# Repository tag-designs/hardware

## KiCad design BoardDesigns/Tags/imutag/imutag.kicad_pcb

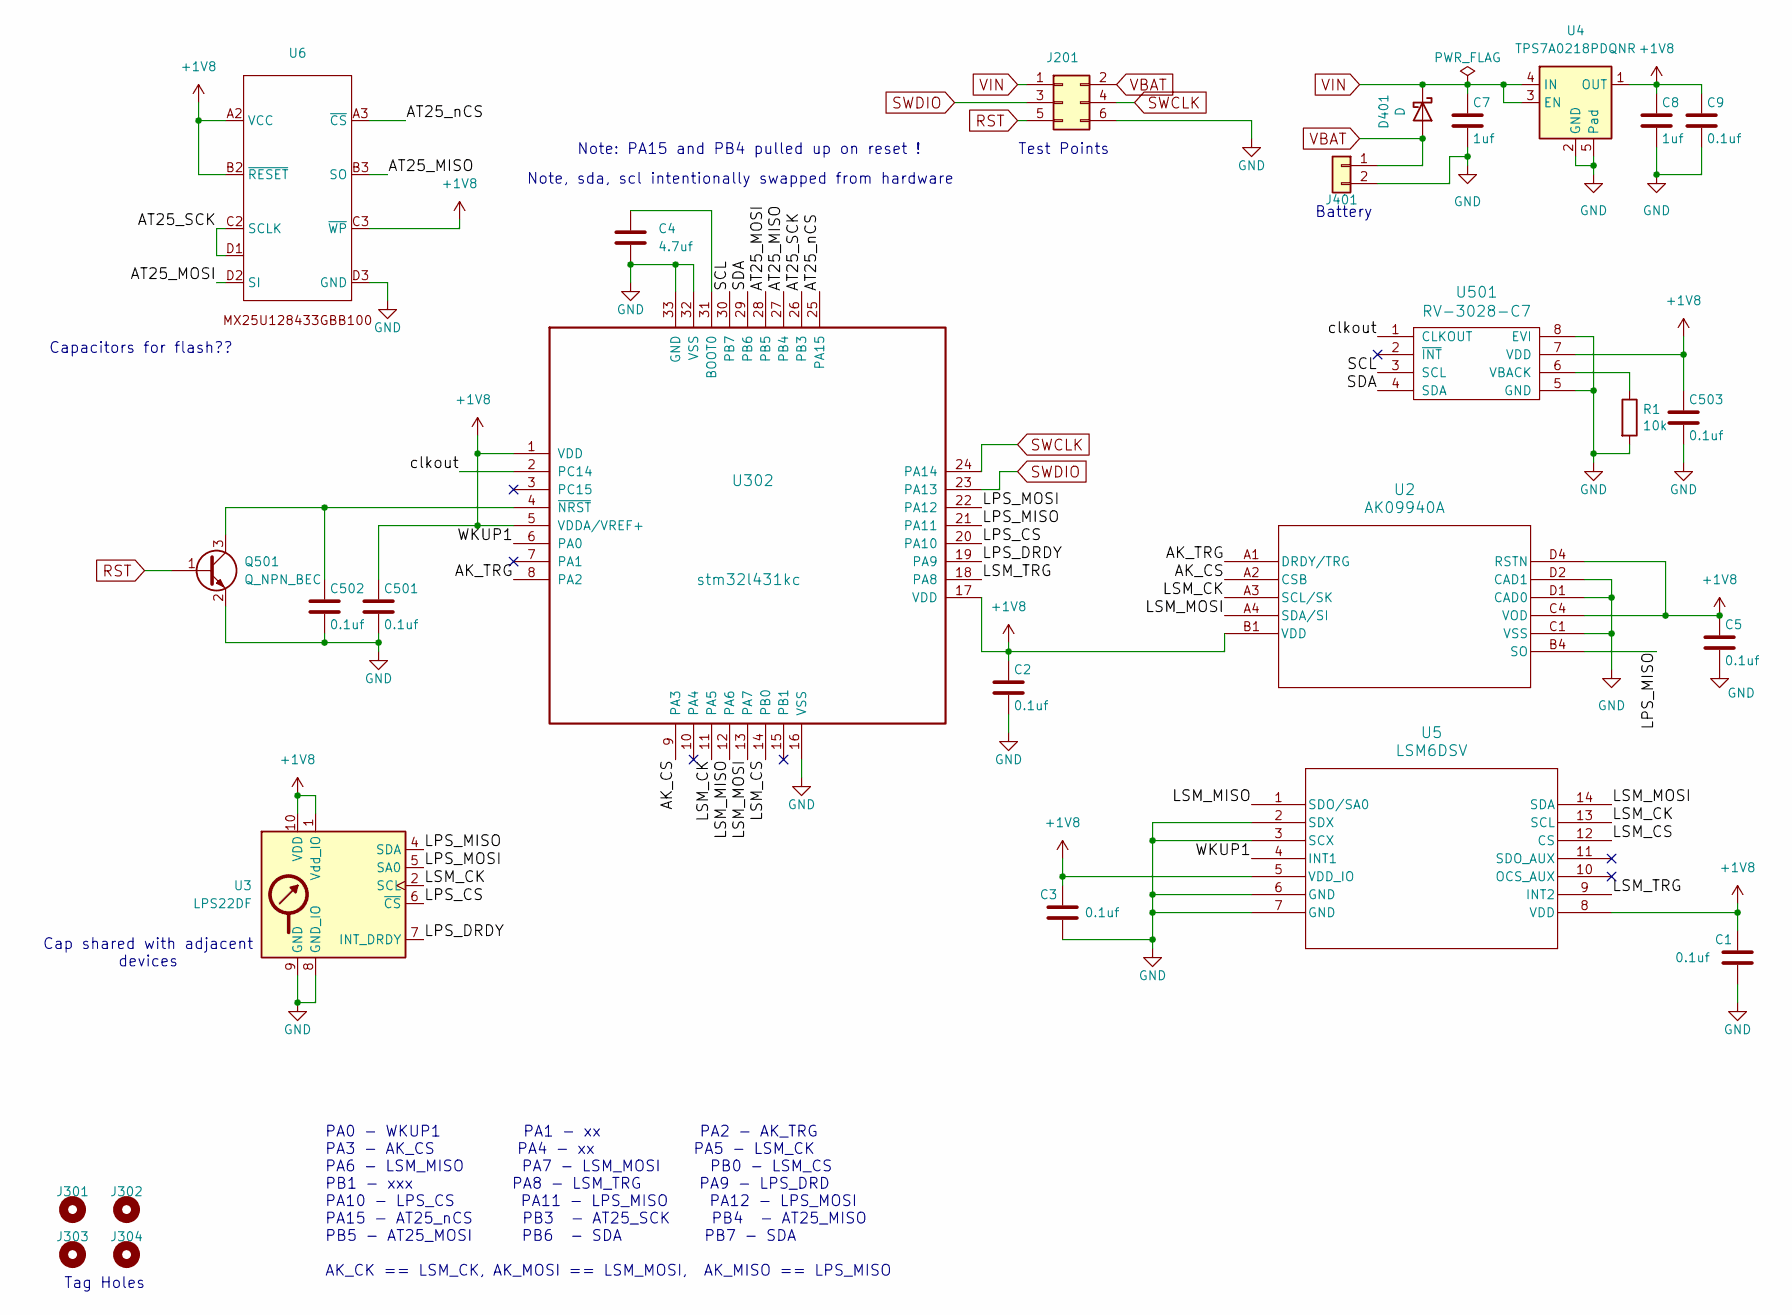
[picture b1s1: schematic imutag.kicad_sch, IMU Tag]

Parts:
C1, C2, C3, C5, C9, C501, C502, C503: 0.1uf; C_0201_0603Metric; MPN GRM033C81E104KE14D; LCSC C181047
C4: 4.7uf; C_0201_0603Metric; MPN GRM035R60J475ME15D; LCSC C335103
C7, C8: 1uf; C_0201_0603Metric; MPN GRM033R60J105MEA2D; LCSC C76930
D401: D; D_0402_1005Metric; MPN CDBQC0130L-HF; LCSC C2886012
J201: CONN_02X04; tagpoints6
J301, J302, J303, J304: Conn_01x01; taghole1.1mm
J401: CONN_01X02; batterypads
Q501: Q_NPN_BEC; SOT-883; MPN BC847AMB,315; LCSC C686658
R1: 10k; R_0201_0603Metric; MPN RC0201FR-0710KL; LCSC C106225
U2: AK09940A; AK09940a; MPN AK09940A
U3: LPS22DF; ST_HLGA-10_2x2mm_P0.5mm_LayoutBorder3x2y
U4: TPS7A0218PDQNR; Texas_X2SON-4_1x1mm_P0.65mm; MPN TPS7A0218PDQNR; LCSC C2862166
U5: LSM6DSV; LGA14-L_2P59X3P1X0P5_STM
U6: IC_MX25U12843GBBI00; MPN MX25U12843GBBI00; LCSC C7316586
U302: stm32l431kc; QFN-32-1EP_5x5mm_P0.5mm_EP3.45x3.45mm; MPN STM32L432KCU6; LCSC C1337280
U501: RV-3028-C7; RV-8803-C7; MPN RV-3028-C7 32.768KHZ 1PPM-TA-QA; LCSC C3019759

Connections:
+1V8: C1.1, C2.1, C3.1, C5.1, C8.1, C9.1, C501.1, C503.1, U2.B1 (VDD), U2.C4 (VOD), U2.D4 (RSTN), U3.1 (Vdd_IO), U3.10 (VDD), U4.1 (OUT), U5.5 (VDD_IO), U5.8 (VDD), U6.A2 (VCC), U6.B2 (~RESET), U6.C3 (~WP), U302.1 (VDD), U302.5 (VDDA/VREF+), U302.17 (VDD), U501.7 (VDD)
/AK_CS: U2.A2 (CSB), U302.9 (PA3)
/AK_TRG: U2.A1 (DRDY/TRG), U302.8 (PA2)
/AT25_MISO: U6.B3 (SO), U302.27 (PB4)
/AT25_MOSI: U6.D2 (SI), U302.28 (PB5)
/AT25_SCK: U6.C2 (SCLK), U6.D1, U302.26 (PB3)
/AT25_nCS: U6.A3 (~CS), U302.25 (PA15)
/LPS_CS: U3.6 (~CS), U302.20 (PA10)
/LPS_DRDY: U3.7 (INT_DRDY), U302.19 (PA9)
/LPS_MISO: U2.B4 (SO), U3.4 (SDA), U302.21 (PA11)
/LPS_MOSI: U3.5 (SA0), U302.22 (PA12)
/LSM_CK: U2.A3 (SCL/SK), U3.2 (SCL), U5.13 (SCL), U302.11 (PA5)
/LSM_CS: U5.12 (CS), U302.14 (PB0)
/LSM_MISO: U5.1 (SDO/SA0), U302.12 (PA6)
/LSM_MOSI: U2.A4 (SDA/SI), U5.14 (SDA), U302.13 (PA7)
/LSM_TRG: U5.9 (INT2), U302.18 (PA8)
/SCL: U302.30 (PB7), U501.3 (SCL)
/SDA: U302.29 (PB6), U501.4 (SDA)
/WKUP1: U5.4 (INT1), U302.6 (PA0)
/clkout: U302.2 (PC14), U501.1 (CLKOUT)
GND: C1.2, C2.2, C3.2, C4.1, C5.2, C7.2, C8.2, C9.2, C501.2, C502.2, C503.2, J201.6, J401.2, Q501.2 (E), R1.2, U2.C1 (VSS), U2.D1 (CAD0), U2.D2 (CAD1), U3.3 (GND), U3.8 (GND_IO), U3.9 (GND), U4.2 (GND), U4.5 (Pad), U5.2 (SDX), U5.3 (SCX), U5.6 (GND), U5.7 (GND), U6.D3 (GND), U302.16 (VSS), U302.32 (VSS), U302.33 (GND), U501.5 (GND), U501.8 (EVI)
unnamed: C502.1, Q501.3 (C), U302.4 (~NRST)
unnamed: C4.2, U302.31 (BOOT0)
unnamed: R1.1, U501.6 (VBACK)
RST: J201.5, Q501.1 (B)
SWCLK: J201.4, U302.24 (PA14)
SWDIO: J201.3, U302.23 (PA13)
VBAT: D401.2 (A), J201.2, J401.1
VIN: C7.1, D401.1 (K), J201.1, U4.3 (EN), U4.4 (IN)

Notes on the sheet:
Note: PA15 and PB4 pulled up on reset !
Capacitors for flash??
Tag Holes
Test Points
PA0 - WKUP1 PA1 - xx PA2 - AK_TRG PA3 - AK_CS PA4 - xx PA5 - LSM_CK PA6 - LSM_MISO PA7 - LSM_MOSI PB0 - LSM_CS PB1 - xxx PA8 - LSM_TRG PA9 - LPS_DRD PA10 - LPS_CS PA11 - LPS_MISO PA12 - LPS_MOSI PA15 - AT25_nCS PB3 - AT25_SCK PB4 - AT25_MISO PB5 - AT25_MOSI PB6 - SDA PB7 - SDA AK_CK == LSM_CK, AK_M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
Battery
Cap shared with adjacent devices
Note, sda, scl intentionally swapped from hardware

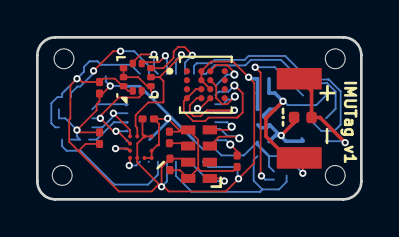
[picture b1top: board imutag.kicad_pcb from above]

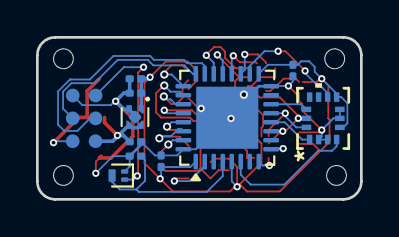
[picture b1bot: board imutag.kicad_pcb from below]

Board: 2 copper layers, 18.0 x 9.0 mm, 27 parts (11 on the bottom side), 29 nets.

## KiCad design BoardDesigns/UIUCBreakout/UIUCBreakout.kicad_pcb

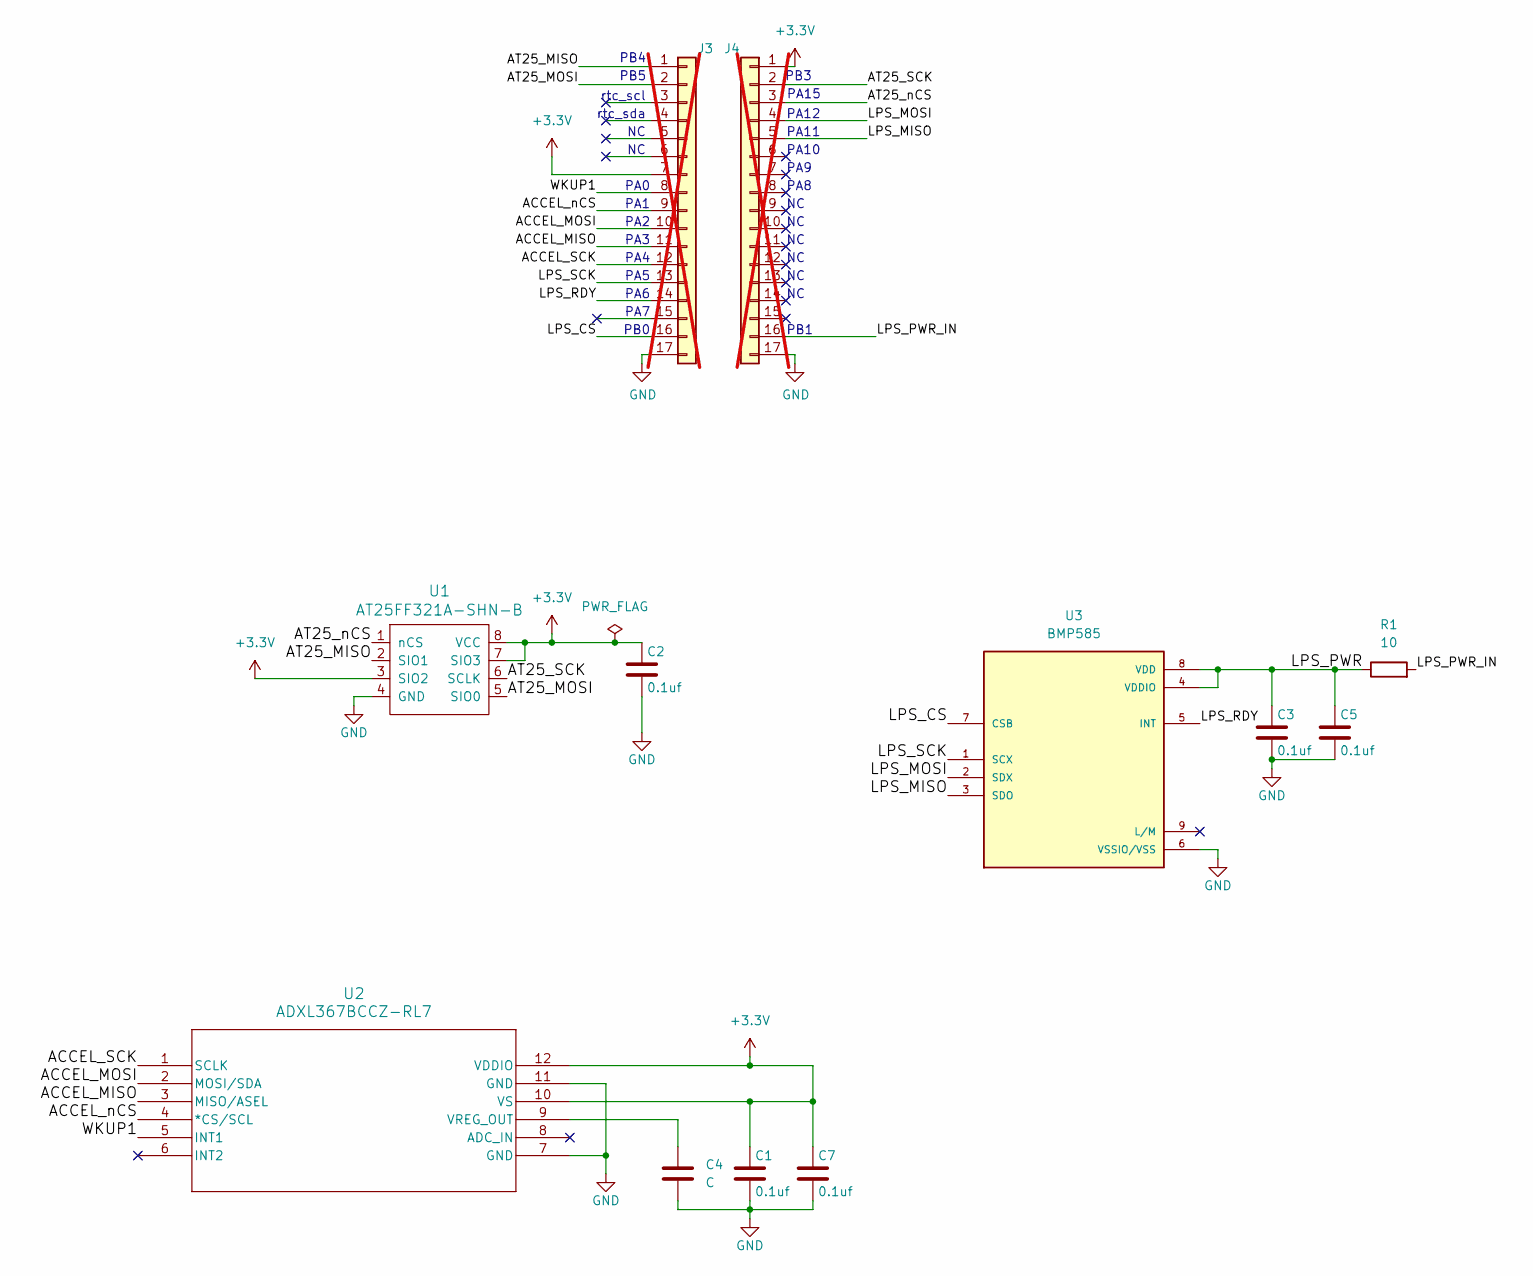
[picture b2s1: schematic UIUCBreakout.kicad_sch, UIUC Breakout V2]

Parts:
C1, C2, C3, C5, C7: 0.1uf; C_0603_1608Metric; MPN CC0603KRX7R9BB104; LCSC C14663
C4: C; C_0603_1608Metric; MPN CL10B224KA8NNNC; LCSC C21120
J3, J4: Conn_01x17; PinHeader_1x17_P2.54mm_Vertical_Staggered; not fitted
R1: 10; R_0603_1608Metric; MPN 0603WAF100JT5E; LCSC C22859
U1: AT25FF321A-SHN-B; SOIC-8_5.3x6.2mm_P1.27mm; MPN AT25FF321A-SHN-B; LCSC C5591126
U2: ADXL367BCCZ-RL7; CC-12-4_ADI; MPN ADXL367BCCZ-RL7; LCSC C17643415
U3: BMP585; LGA9_BMP585_BOS; PARTREV 1.2; LCSC C18184976

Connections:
+3.3V: C1.1, C2.1, C7.1, J3.7, J4.1, U1.3 (SIO2), U1.7 (SIO3), U1.8 (VCC), U2.10 (VS), U2.12 (VDDIO); also elsewhere on the board
/ACCEL_MISO: J3.11, U2.3 (MISO/ASEL)
/ACCEL_MOSI: J3.10, U2.2 (MOSI/SDA)
/ACCEL_SCK: J3.12, U2.1 (SCLK)
/ACCEL_nCS: J3.9, U2.4 (*CS/SCL)
/AT25_MISO: J3.1, U1.2 (SIO1)
/AT25_MOSI: J3.2, U1.5 (SIO0)
/AT25_SCK: J4.2, U1.6 (SCLK)
/AT25_nCS: J4.3, U1.1 (nCS)
/LPS_CS: J3.16, U3.7 (CSB)
/LPS_MISO: J4.5, U3.3 (SDO)
/LPS_MOSI: J4.4, U3.2 (SDX)
/LPS_PWR: C3.1, C5.1, R1.1, U3.4 (VDDIO), U3.8 (VDD)
/LPS_PWR_IN: J4.16, R1.2
/LPS_RDY: J3.14, U3.5 (INT)
/LPS_SCK: J3.13, U3.1 (SCX)
/WKUP1: J3.8, U2.5 (INT1)
GND: C1.2, C2.2, C3.2, C4.2, C5.2, C7.2, J3.17, J4.17, U1.4 (GND), U2.7 (GND), U2.11 (GND), U3.6 (VSSIO/VSS); also elsewhere on the board
unnamed: C4.1, U2.9 (VREG_OUT)

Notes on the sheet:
PA1
PA9
PA2
PA0
PA8
PA7
PA15
PA5
PA4
PB3
PA6
PA3
PB4
PA12
PB0
PB5
PA10
rtc_sda
PA11
PB1
rtc_scl

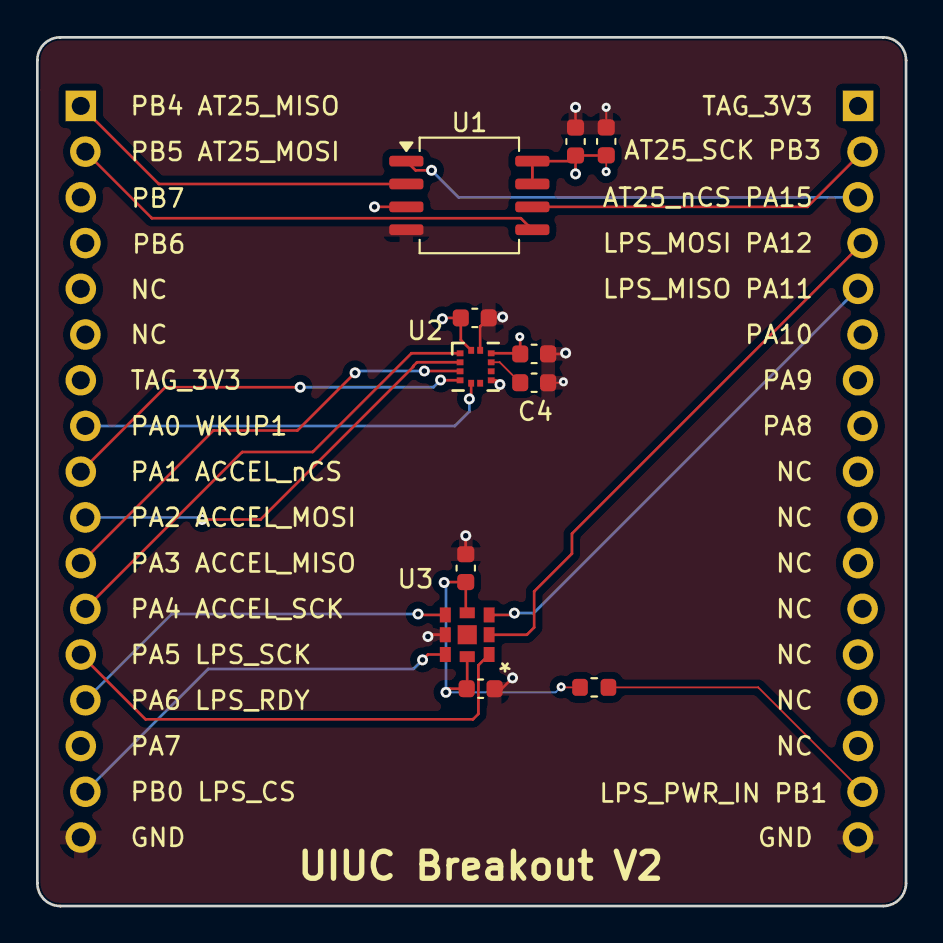
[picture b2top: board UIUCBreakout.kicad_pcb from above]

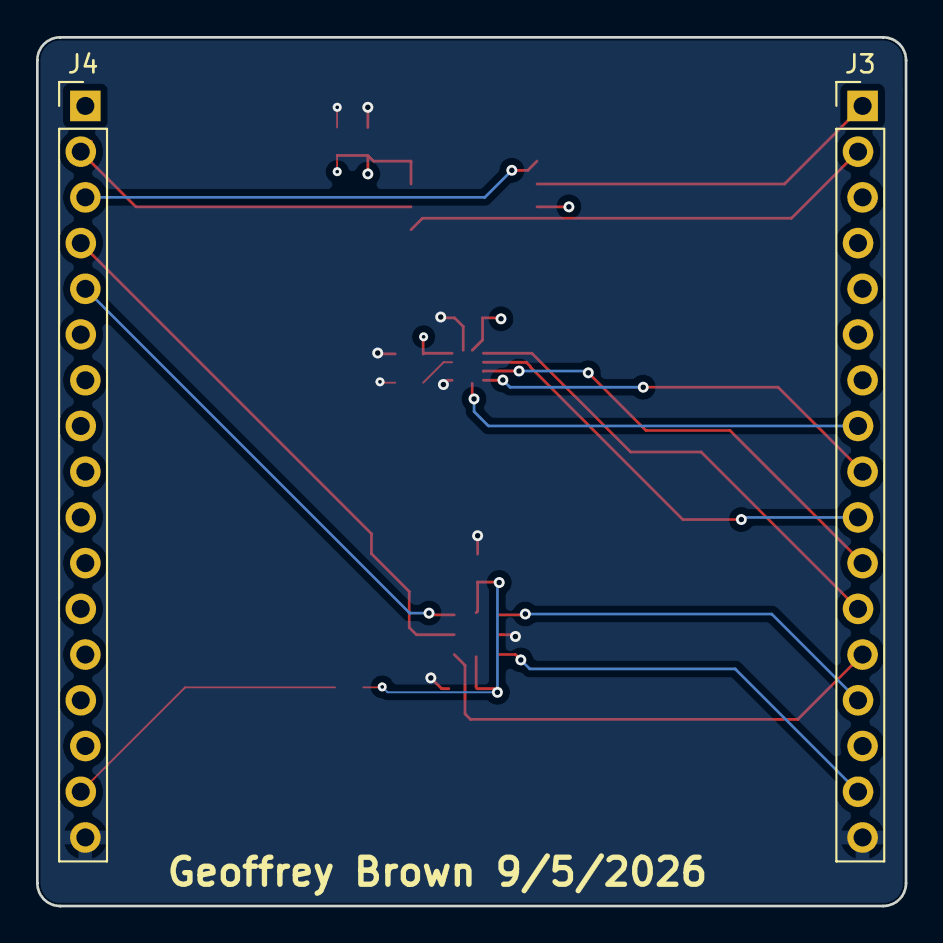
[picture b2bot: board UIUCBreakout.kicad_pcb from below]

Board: 4 copper layers, 48.3 x 48.3 mm, 13 parts (2 on the bottom side), 19 nets.

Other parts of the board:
C6: 4.7uf; C_0603_1608Metric

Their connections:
+3.3V: C6.1; also elsewhere on the board
GND: C6.2; also elsewhere on the board

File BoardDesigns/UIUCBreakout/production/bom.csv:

Designator,Footprint,Quantity,Value,LCSC Part #
"C1, C2, C3, C5, C7",0603,5,0.1uf,C14663
U1,SOIC-8_5.3x6.2mm_P1.27mm,1,AT25FF321A-SHN-B,C5591126
U2,CC-12-4_ADI,1,ADXL367BCCZ-RL7,C17643415
U3,LGA9_BMP585_BOS,1,BMP585,C18184976

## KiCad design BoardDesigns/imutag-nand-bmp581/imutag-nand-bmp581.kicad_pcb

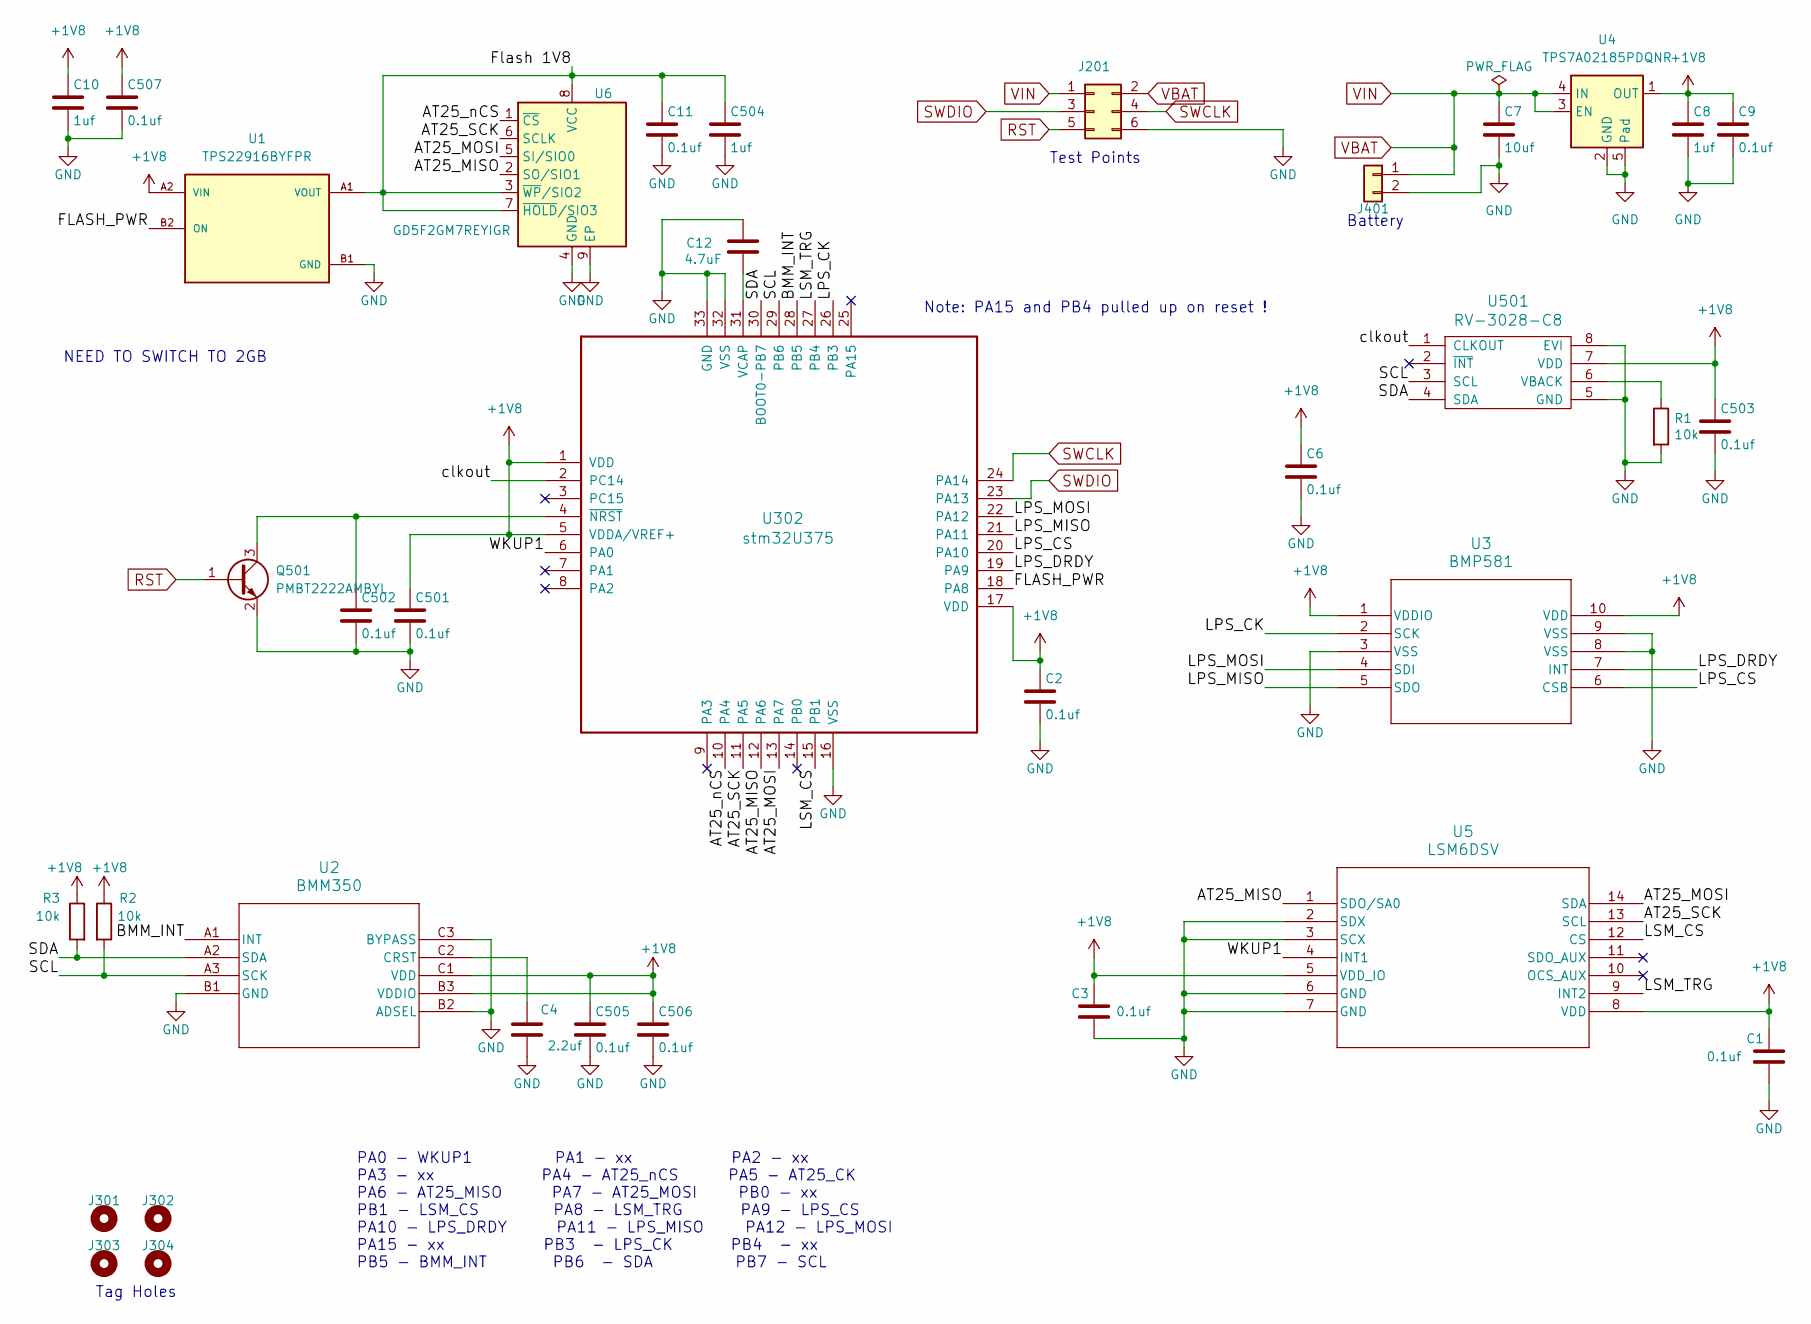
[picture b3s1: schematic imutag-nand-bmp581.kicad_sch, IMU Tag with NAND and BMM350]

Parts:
C1, C2, C3, C6, C9, C11, C501, C502, C503, C505, C506, C507: 0.1uf; C_0201_0603Metric; MPN GRM033C81E104KE14D; LCSC C181047
C4: 2.2uf; C_0402_1005Metric; MPN GRM155R6YA225KE11D; LCSC C237392
C7: 10uf; C_0603_1608Metric; MPN GRM188R61E106MA73D; LCSC C91606
C8, C10, C504: 1uf; C_0201_0603Metric; MPN GRM033R60J105MEA2D; LCSC C76930
C12: 4.7uF; C_0402_1005Metric; MPN CL05A475MP5NRNC; LCSC C23733
J201: CONN_02X04; tagpoints6
J301, J302, J303, J304: Conn_01x01; taghole1.1mm
J401: CONN_01X02; batterypads
Q501: PMBT2222AMBYL; SOT-883; MPN PMBT2222AMBYL; LCSC C552701
R1, R2, R3: 10k; R_0201_0603Metric; MPN RC0201FR-0710KL; LCSC C106225
U1: TPS22916BYFPR; IC_TPS22916BYFPR; PARTREV F; LCSC C2150095
U2: BMM350; BGA9_BMM350_BOS; MPN BMM350; LCSC C17225907
U3: BMP581; QFN10_BMP581_BOS; MPN BMP581; LCSC C5362283
U4: TPS7A02185PDQNR; Texas_X2SON-4_1x1mm_P0.65mm; MPN TPS7A02185PDQNR; LCSC C2864496
U5: LSM6DSV; LGA14-L_2P59X3P1X0P5_STM; MPN LSM6DSV; LCSC C5267399
U6: GD5F2GM7REYIGR; WSON-8-1EP_8x6mm_P1.27mm_EP3.4x4.3mm; MPN GD5F2GM7REYIGR; LCSC C23706308
U302: stm32U375; UFQFPN-32-1EP_5x5mm_P0.5mm_EP3.5x3.5mm; MPN STM32U375KGU6; LCSC C45338536
U501: RV-3028-C8; MPN RV-3028-C8-32.768kHz-1PPM-TA-QC; LCSC C46471039

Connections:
+1V8: C1.1, C2.1, C3.1, C6.1, C8.1, C9.1, C10.1, C501.1, C503.1, C505.1, C506.1, C507.1, R2.1, R3.1, U1.A2 (VIN), U2.B3 (VDDIO), U2.C1 (VDD), U3.1 (VDDIO), U3.10 (VDD), U4.1 (OUT), U5.5 (VDD_IO), U5.8 (VDD), U302.1 (VDD), U302.5 (VDDA/VREF+), U302.17 (VDD), U501.7 (VDD)
/AT25_MISO: U5.1 (SDO/SA0), U6.2 (SO/SIO1), U302.12 (PA6)
/AT25_MOSI: U5.14 (SDA), U6.5 (SI/SIO0), U302.13 (PA7)
/AT25_SCK: U5.13 (SCL), U6.6 (SCLK), U302.11 (PA5)
/AT25_nCS: U6.1 (~CS), U302.10 (PA4)
/BMM_INT: U2.A1 (INT), U302.28 (PB5)
/FLASH_PWR: U1.B2 (ON), U302.18 (PA8)
/Flash 1V8: C11.1, C504.1, U1.A1 (VOUT), U6.3 (~WP/SIO2), U6.7 (~HOLD/SIO3), U6.8 (VCC)
/LPS_CK: U3.2 (SCK), U302.26 (PB3)
/LPS_CS: U3.6 (CSB), U302.20 (PA10)
/LPS_DRDY: U3.7 (INT), U302.19 (PA9)
/LPS_MISO: U3.5 (SDO), U302.21 (PA11)
/LPS_MOSI: U3.4 (SDI), U302.22 (PA12)
/LSM_CS: U5.12 (CS), U302.15 (PB1)
/LSM_TRG: U5.9 (INT2), U302.27 (PB4)
/SCL: R2.2, U2.A3 (SCK), U302.29 (PB6), U501.3 (SCL)
/SDA: R3.2, U2.A2 (SDA), U302.30 (BOOT0-PB7), U501.4 (SDA)
/WKUP1: U5.4 (INT1), U302.6 (PA0)
/clkout: U302.2 (PC14), U501.1 (CLKOUT)
GND: C1.2, C2.2, C3.2, C4.2, C6.2, C7.2, C8.2, C9.2, C10.2, C11.2, C12.1, C501.2, C502.2, C503.2, C504.2, C505.2, C506.2, C507.2, J201.6, J401.2, Q501.2 (E), R1.2, U1.B1 (GND), U2.B1 (GND), U2.B2 (ADSEL), U2.C3 (BYPASS), U3.3 (VSS), U3.8 (VSS), U3.9 (VSS), U4.2 (GND), U4.5 (Pad), U5.2 (SDX), U5.3 (SCX), U5.6 (GND), U5.7 (GND), U6.4 (GND), U6.9 (EP), U302.16 (VSS), U302.32 (VSS), U302.33 (GND), U501.5 (GND), U501.8 (EVI)
unnamed: C502.1, Q501.3 (C), U302.4 (~NRST)
unnamed: C4.1, U2.C2 (CRST)
unnamed: C12.2, U302.31 (VCAP)
unnamed: R1.1, U501.6 (VBACK)
RST: J201.5, Q501.1 (B)
SWCLK: J201.4, U302.24 (PA14)
SWDIO: J201.3, U302.23 (PA13)
VBAT: C7.1, J201.1, J201.2, J401.1, U4.3 (EN), U4.4 (IN)

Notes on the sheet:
Note: PA15 and PB4 pulled up on reset !
Tag Holes
NEED TO SWITCH TO 2GB
Test Points
PA0 - WKUP1 PA1 - xx PA2 - xx PA3 - xx PA4 - AT25_nCS PA5 - AT25_CK PA6 - AT25_MISO PA7 - AT25_MOSI PB0 - xx PB1 - LSM_CS PA8 - LSM_TRG PA9 - LPS_CS PA10 - LPS_DRDY PA11 - LPS_MISO PA12 - LPS_MOSI PA15 - xx PB3 - LPS_CK PB4 - xx PB5 - BMM_INT PB6 - SDA PB7 - SCL
Battery

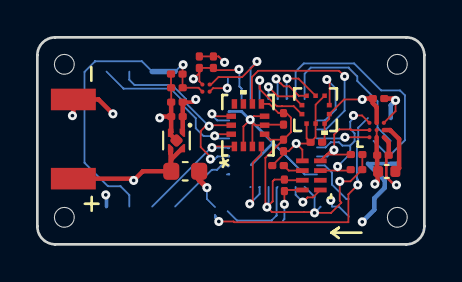
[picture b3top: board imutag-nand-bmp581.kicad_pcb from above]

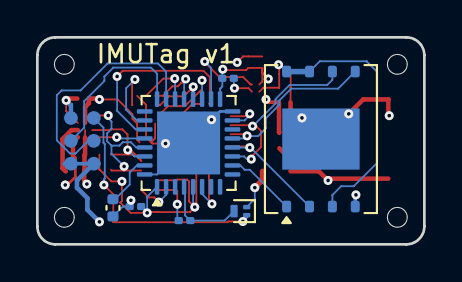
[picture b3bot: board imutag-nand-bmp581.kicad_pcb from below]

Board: 4 copper layers, 21.5 x 11.5 mm, 36 parts (8 on the bottom side), 28 nets.

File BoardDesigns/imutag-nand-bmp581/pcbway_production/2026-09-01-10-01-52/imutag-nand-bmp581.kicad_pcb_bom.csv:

Designator,Quantity,Value,Footprint,Package,MPN,DNP,Mount_Type,DISTPN,LCSC,MFN,KiLib_Generator,Macrofab,Description,Sim.Device,Sim.Pins,MAXIMUM_PACKAGE_HEIGHT,CREATOR,STANDARD,PARTREV,MANUFACTURER
"C1, C11, C2, C3, C501, C502, C503, C505, C506, C507, C6, C9",12,0.1uf,C_0201_0603Metric,,GRM033C81E104KE14D,,smt,[C9]490-10403-1-ND; [C6]490-7229-2-ND,C181047,Murata,SMD_2terminal_chip_molded,MF-CAP-0402-0.1uF,,,,,,,,
"C10, C504, C8",3,1uf,C_0201_0603Metric,,GRM033R60J105MEA2D,,smt,490-7229-1-ND,C76930,Murata,SMD_2terminal_chip_molded,,,,,,,,,
C12,1,4.7uF,C_0402_1005Metric,,CL05A475MP5NRNC,,smt,,C23733,Samsung Electro-Mechanics,SMD_2terminal_chip_molded,,Unpolarized capacitor,,,,,,,
C4,1,2.2uf,C_0402_1005Metric,,GRM155Z71A225KE01D,,smt,,C2997286,Murata,SMD_2terminal_chip_molded,,Unpolarized capacitor,,,,,,,
C7,1,10uf,C_0603_1608Metric,,GRM188R61E106MA73D,,smt,,C91606,Murata,SMD_2terminal_chip_molded,,,,,,,,,
Q501,1,PMBT2222AMBYL,SOT-883,,PMBT2222AMBYL,,smt,1727-PMBT2222AMBYLCT-ND,C552701,Nexperia,,,"NPN transistor, base/emitter/collector",NPN,1=B 2=E 3=C,,,,,
"R1, R2, R3",3,10k,R_0201_0603Metric,,RC0201FR-0710KL,,smt,311-10.0KMCT-ND,C106225,Yaego,SMD_2terminal_chip_molded,MF-RES-0402-10K,Resistor,,,,,,,
U1,1,TPS22916BYFPR,IC_TPS22916BYFPR,,TPS22916BYFPR,,smt,,C2150095,Texas Instruments,,,,,,0.5mm,DIZAR,Manufacturer Recommendations,F,Texas Instruments
U2,1,BMM350,BGA9_BMM350_BOS,,BMM350,,smt,,C17225907,Bosch Sensortec,,,,,,,,,,
U3,1,BMP581,QFN10_BMP581_BOS,,BMP581,,smt,,C5362283,Bosch,,,,,,,,,,
U302,1,stm32U375,UFQFPN-32-1EP_5x5mm_P0.5mm_EP3.5x3.5mm,,STM32U375KGU6,,smt,,C45338536,STMicroelectronics,package/no_lead,,,,,,,,,
U4,1,TPS7A02185PDQNR,Texas_X2SON-4_1x1mm_P0.65mm,,TPS7A02185PDQNR,,smt,296-TPS7A2018PDQNRCT-ND,C2864496,Texas Instruments,,,"300 mA Low Dropout Voltage Regulator, Fixed Output, 1.6..6.0Vin, Low-Noise (7μV RMS), 6.5μA IQ LDO, X2SON-5",,,,,,,
U5,1,LSM6DSV,LGA14-L_2P59X3P1X0P5_STM,,LSM6DSV,,smt,,C5267399,STM microelectronics,,,,,,,,,,
U501,1,RV-3028-C8-32.768kHz-1PPM-TA-QC,RV-3028-C8,,RV-3028-C8-32.768kHz-1PPM-TA-QC,,smt,,C46471039,Micro Crystal,,,,,,,,,,
U6,1,GD5F2GM7REYIGR,WSON-8-1EP_8x6mm_P1.27mm_EP3.4x4.3mm,,GD5F2GM7REYIGR,,smt,,C23706308,GigaDevice Semicon Beijing,package/no_lead,,"1-Gbit 1.8V SPI Serial Flash Memory, WSON-8",,,,,,,

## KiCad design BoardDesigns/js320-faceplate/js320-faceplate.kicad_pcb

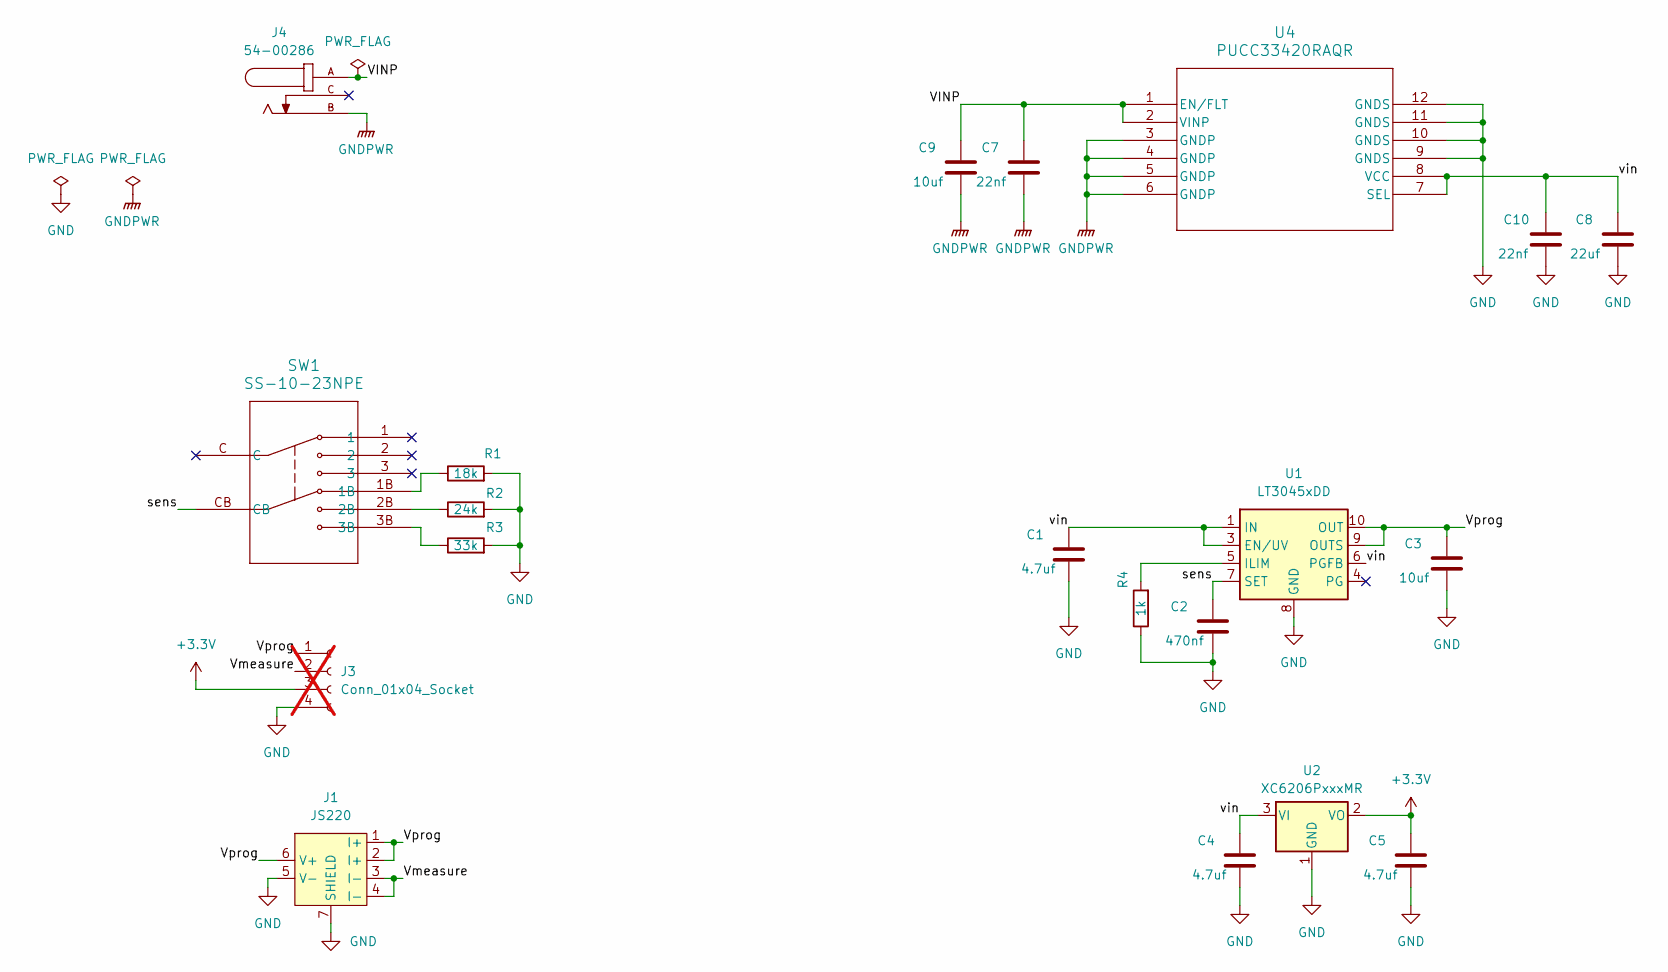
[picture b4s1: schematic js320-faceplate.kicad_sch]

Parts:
C1, C4, C5: 4.7uf; C_0805_2012Metric; MPN CL21A475KAQNNNE; LCSC C1779
C2: 470nf; C_0805_2012Metric; MPN CL21B474KBFNNNE; LCSC C13967
C3, C9: 10uf; C_0805_2012Metric; MPN CL21A106KAYNNNE; LCSC C15850
C7, C10: 22nf; C_0402_1005Metric; MPN 0402B223K500NT; LCSC C1532
C8: 22uf; C_0805_2012Metric; MPN CL21A226MAQNNNE; LCSC C45783
J1: JS220; MPN TSM-103-01-S-DV-A; LCSC C20990825
J3: Conn_01x04_Socket; JST_XH_B4B-XH-AM_1x04_P2.50mm_Vertical; not fitted
J4: 54-00286; TENSILITY_54-00286; PARTREV A
R1: 18k; R_0805_2012Metric; MPN PTFR0805B18K0N9; LCSC C351602
R2: 24k; R_0805_2012Metric; MPN PTFR0805B24K9N9; LCSC C2692770
R3: 33k; R_0805_2012Metric; MPN PTFR0805B33K0N9; LCSC C351577
R4: 1k; R_0805_2012Metric; MPN 0805W8F1001T5E; LCSC C17513
SW1: SS-10-23NPE; SS-10-23-NP_NDC; MPN SS-10-23NP-LE
U1: LT3045xDD; DFN-10-1EP_3x3mm_P0.5mm_EP1.65x2.38mm; MPN LT3045EDD#TRPBF; LCSC C514420
U2: XC6206PxxxMR; SOT-23-3; MPN XC6206P332MR-G; LCSC XC6206P332MR-G
U4: PUCC33420RAQR; VSON-FCRLF12_RAQ_TEX; MPN UCC33420RAQR; LCSC C46461551

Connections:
+3.3V: C5.1, J3.3, U2.2 (VO)
/VINP: C7.1, C9.1, J4.A, U4.1 (EN/FLT), U4.2 (VINP)
/Vmeasure: J1.3 (I-), J1.4 (I-), J3.2
/Vprog: C3.1, J1.1 (I+), J1.2 (I+), J1.6 (V+), J3.1, U1.9 (OUTS), U1.10 (OUT)
/sens: C2.1, SW1.CB, U1.7 (SET)
/vin: C1.1, C4.1, C8.1, C10.1, U1.1 (IN), U1.2 (IN), U1.3 (EN/UV), U1.6 (PGFB), U2.3 (VI), U4.7 (SEL), U4.8 (VCC)
GND: C1.2, C2.2, C3.2, C4.2, C5.2, C8.2, C10.2, J1.5 (V-), J1.7 (SHIELD), J3.4, R1.2, R2.2, R3.2, R4.1, U1.8 (GND), U1.11 (GND), U2.1 (GND), U4.9 (GNDS), U4.10 (GNDS), U4.11 (GNDS), U4.12 (GNDS)
GNDPWR: C7.2, C9.2, J4.B, U4.3 (GNDP), U4.4 (GNDP), U4.5 (GNDP), U4.6 (GNDP)
unnamed: R1.1, SW1.1B
unnamed: R2.1, SW1.2B
unnamed: R3.1, SW1.3B
unnamed: R4.2, U1.5 (ILIM)

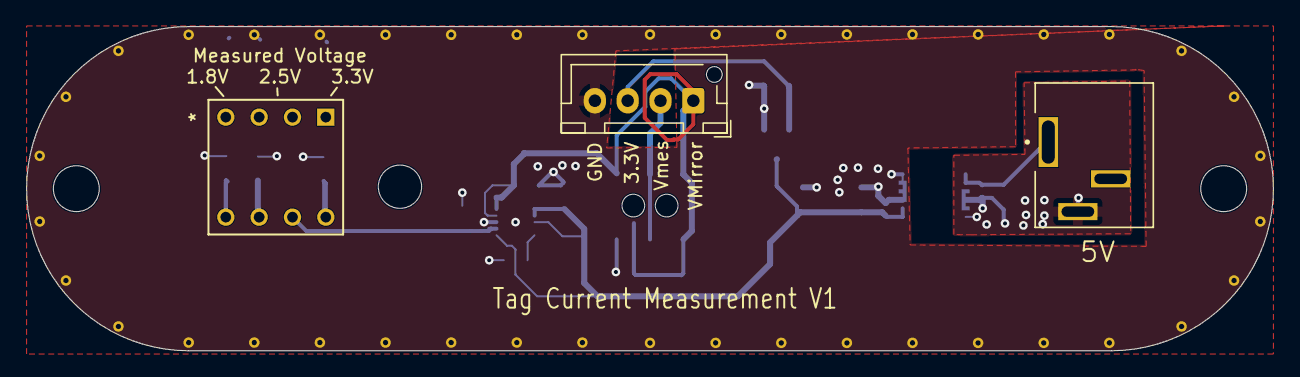
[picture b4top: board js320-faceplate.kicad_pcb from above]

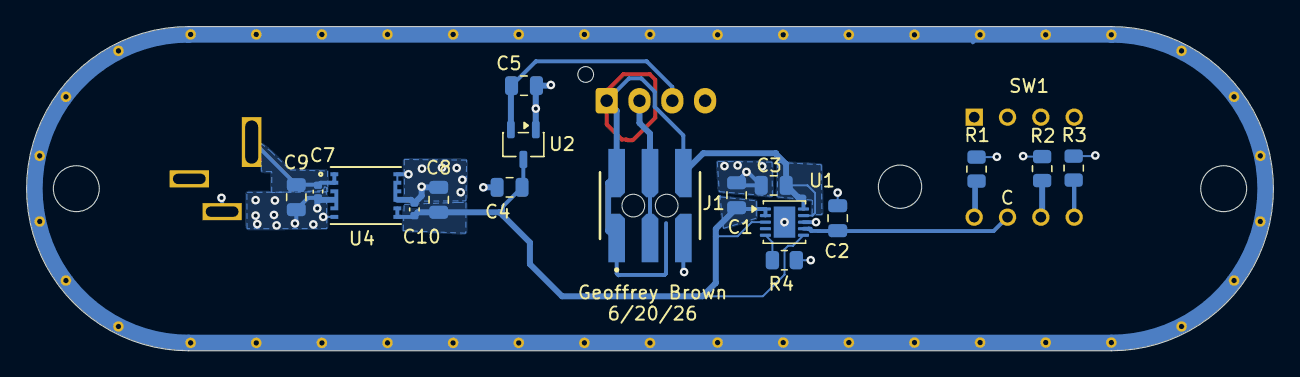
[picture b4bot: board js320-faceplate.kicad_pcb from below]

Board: 2 copper layers, 95.0 x 24.7 mm, 20 parts (16 on the bottom side), 12 nets.
